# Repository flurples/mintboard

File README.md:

# mintboard
a 40% bluetooth keyboard built into an altoids tin

build video: https://youtu.be/VZ1lAV-ThZo

## you will need
- an altoids tin
- a mintboard pcb (with diodes and switches)
- 1x top and 1x bottom housings
- keycaps ( 32x 1u, 2x 1.25u, 4x 1.5u, 2x 1.75u, 1x 4u)
- a nice!nano
- a small battery (I used a [301230](https://typeractive.xyz/products/lithium-battery-110mah?_pos=1&_sid=1f1b588b2&_ss=r) 110 mah lithium battery from typeractive)
- a [OS202011MA0QN1](https://www.digikey.com/en/products/detail/c-k/OS202011MA0QN1/1981434?so=84718120&content=productdetail_US&mkt_tok=MDI4LVNYSy01MDcAAAGQVwdjiVGonvzkfjpSeKMOLfsL14AKEAxTyVseBkvXUuhdkCoQ9XYS7CoJXYxmb_hU999OJmHqsBVxQt5MaQLbL1UVmK6itZdC7dEBY8wV) or equivalent power switch
- 4x m2 screws
- double sided tape
- a dremel or something to cut the altoids tin with

## notes
- pcb production files can be found in mintboard/pcb/production
- bom files were created for jlcpcb's parts library in 2023; double check correct components before ordering
- use the provided .uf2 file to flash the nice!nano, or build your own firmware if you want. the zmk build files were made for an older version of zmk so they will likely not work without some modification.

## disclaimer
I do not sell any products, and I am not affiliated with any vendors who claim to sell my designs. if you choose to support these vendors, I am not responsible for any issues you may encounter with them.

## gallery

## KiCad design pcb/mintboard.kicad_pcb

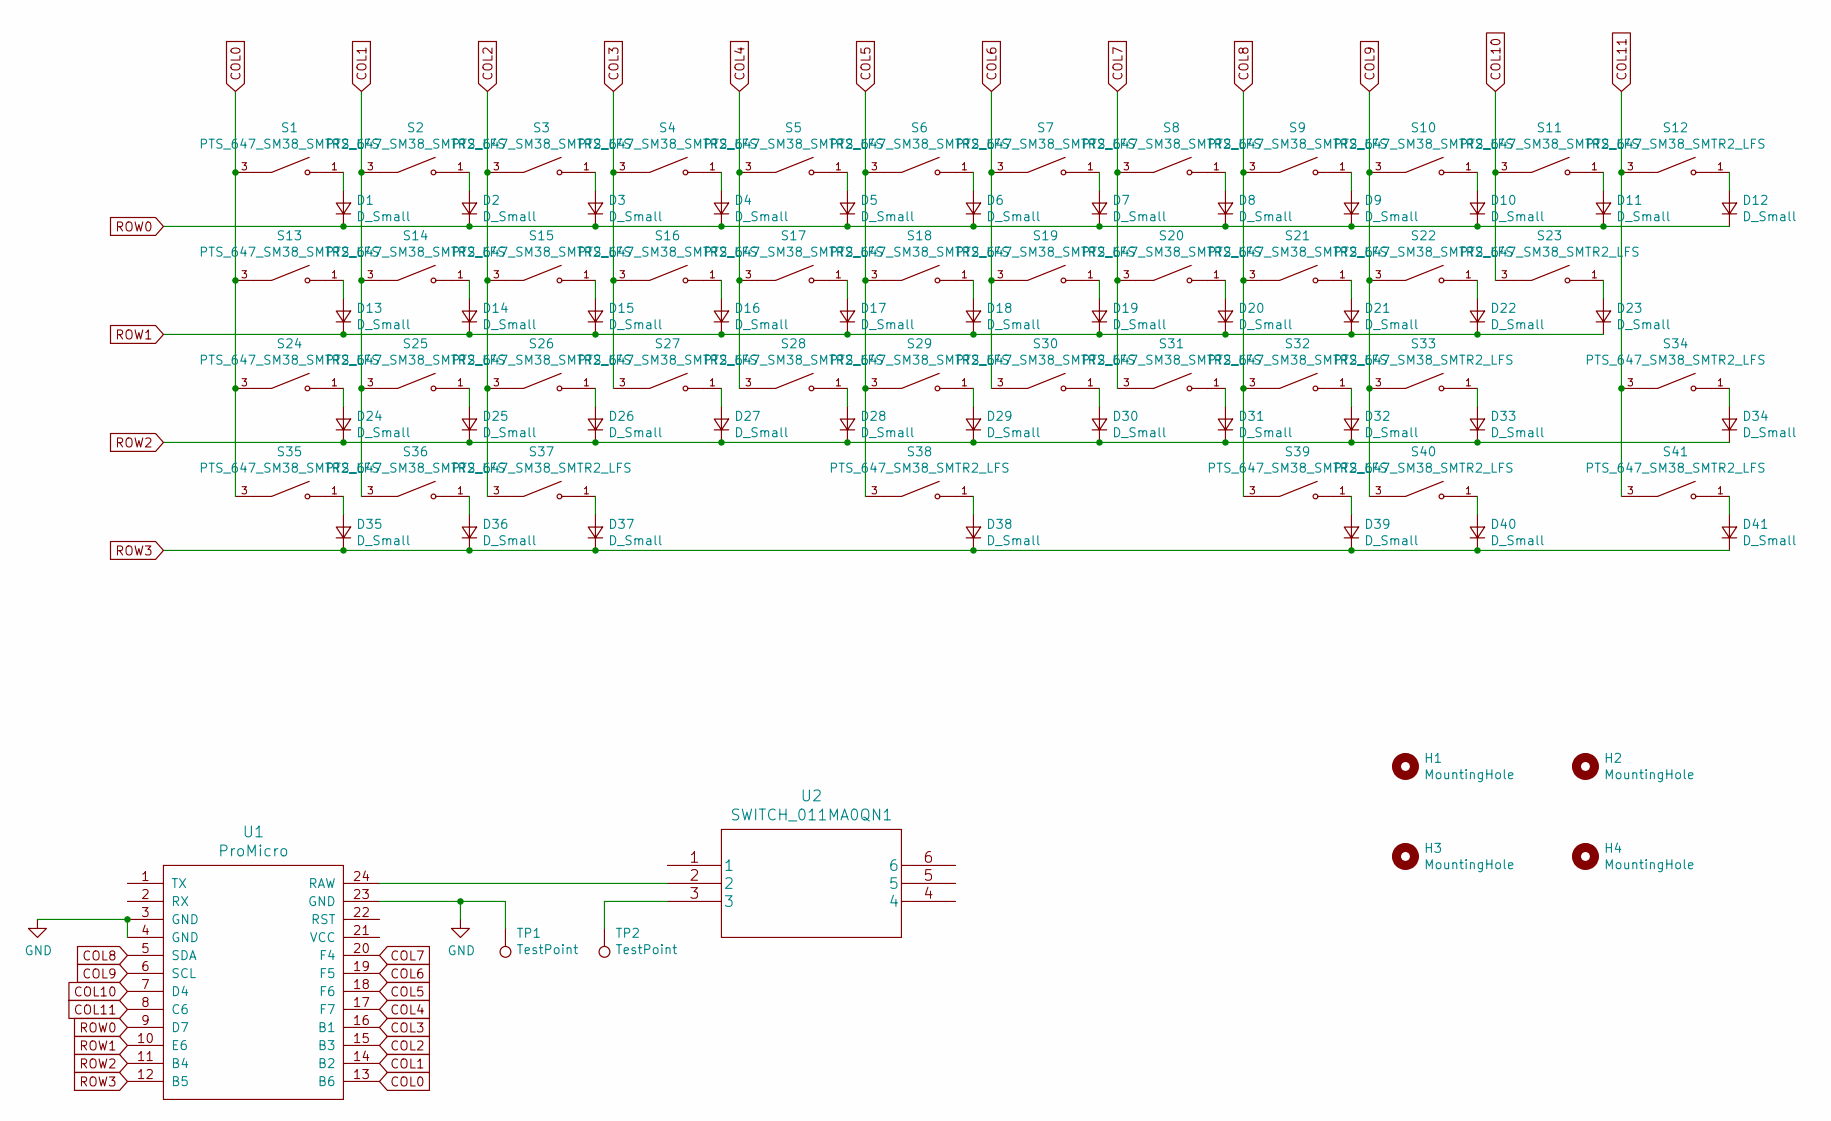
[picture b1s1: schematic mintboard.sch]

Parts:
D1, D2, D3, D4, D5, D6, D7, D8, D9, D10, D11, D12, D13, D14, D15, D16, D17, D18, D19, D20, D21, D22, D23, D24, D25, D26, D27, D28, D29, D30, D31, D32, D33, D34, D35, D36, D37, D38, D39, D40, D41: D_Small; D_SOD-123
H1, H2, H3, H4: MountingHole; MountingHole_2.5mm
S1, S2, S3, S4, S5, S6, S7, S8, S9, S10, S11, S12, S13, S14, S15, S16, S17, S18, S19, S20, S21, S22, S23, S24, S25, S26, S27, S28, S29, S30, S31, S32, S33, S34, S35, S36, S37, S38, S39, S40, S41: PTS_647_SM38_SMTR2_LFS; SW_PTS_647_SM38_SMTR2_LFS_1133; PARTREV 11 Jun 19
TP1, TP2: TestPoint; TestPoint_THTPad_D2.0mm_Drill1.0mm
U1: ProMicro; ProMicro-SMD
U2: SWITCH_011MA0QN1; OS202011MA0QN1

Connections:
COL0: S1.3, S13.3, S24.3, S35.3, U1.13 (B6)
COL1: S2.3, S14.3, S25.3, S36.3, U1.14 (B2)
COL2: S3.3, S15.3, S26.3, S37.3, U1.15 (B3)
COL3: S4.3, S16.3, S27.3, U1.16 (B1)
COL4: S5.3, S17.3, S28.3, U1.17 (F7)
COL5: S6.3, S18.3, S29.3, S38.3, U1.18 (F6)
COL6: S7.3, S19.3, S30.3, U1.19 (F5)
COL7: S8.3, S20.3, S31.3, U1.20 (F4)
COL8: S9.3, S21.3, S32.3, S39.3, U1.5 (SDA)
COL9: S10.3, S22.3, S33.3, S40.3, U1.6 (SCL)
COL10: S11.3, S23.3, U1.7 (D4)
COL11: S12.3, S34.3, S41.3, U1.8 (C6)
GND: TP1.1, U1.3 (GND), U1.4 (GND), U1.23 (GND)
unnamed: D1.2 (A), S1.1
unnamed: D2.2 (A), S2.1
unnamed: D3.2 (A), S3.1
unnamed: D4.2 (A), S4.1
unnamed: D5.2 (A), S5.1
unnamed: D6.2 (A), S6.1
unnamed: D7.2 (A), S7.1
unnamed: D8.2 (A), S8.1
unnamed: D9.2 (A), S9.1
unnamed: D10.2 (A), S10.1
unnamed: D11.2 (A), S11.1
unnamed: D12.2 (A), S12.1
unnamed: D13.2 (A), S13.1
unnamed: D14.2 (A), S14.1
unnamed: D15.2 (A), S15.1
unnamed: D16.2 (A), S16.1
unnamed: D17.2 (A), S17.1
unnamed: D18.2 (A), S18.1
unnamed: D19.2 (A), S19.1
unnamed: D20.2 (A), S20.1
unnamed: D21.2 (A), S21.1
unnamed: D22.2 (A), S22.1
unnamed: D23.2 (A), S23.1
unnamed: D24.2 (A), S24.1
unnamed: D25.2 (A), S25.1
unnamed: D26.2 (A), S26.1
unnamed: D27.2 (A), S27.1
unnamed: D28.2 (A), S28.1
unnamed: D29.2 (A), S29.1
unnamed: D30.2 (A), S30.1
unnamed: D31.2 (A), S31.1
unnamed: D32.2 (A), S32.1
unnamed: D33.2 (A), S33.1
unnamed: D34.2 (A), S34.1
unnamed: D35.2 (A), S35.1
unnamed: D36.2 (A), S36.1
unnamed: D37.2 (A), S37.1
unnamed: D38.2 (A), S38.1
unnamed: D39.2 (A), S39.1
unnamed: D40.2 (A), S40.1
unnamed: D41.2 (A), S41.1
unnamed: TP2.1, U2.3
unnamed: U1.24 (RAW), U2.2
ROW0: D1.1 (K), D2.1 (K), D3.1 (K), D4.1 (K), D5.1 (K), D6.1 (K), D7.1 (K), D8.1 (K), D9.1 (K), D10.1 (K), D11.1 (K), D12.1 (K), U1.9 (D7)
ROW1: D13.1 (K), D14.1 (K), D15.1 (K), D16.1 (K), D17.1 (K), D18.1 (K), D19.1 (K), D20.1 (K), D21.1 (K), D22.1 (K), D23.1 (K), U1.10 (E6)
ROW2: D24.1 (K), D25.1 (K), D26.1 (K), D27.1 (K), D28.1 (K), D29.1 (K), D30.1 (K), D31.1 (K), D32.1 (K), D33.1 (K), D34.1 (K), U1.11 (B4)
ROW3: D35.1 (K), D36.1 (K), D37.1 (K), D38.1 (K), D39.1 (K), D40.1 (K), D41.1 (K), U1.12 (B5)

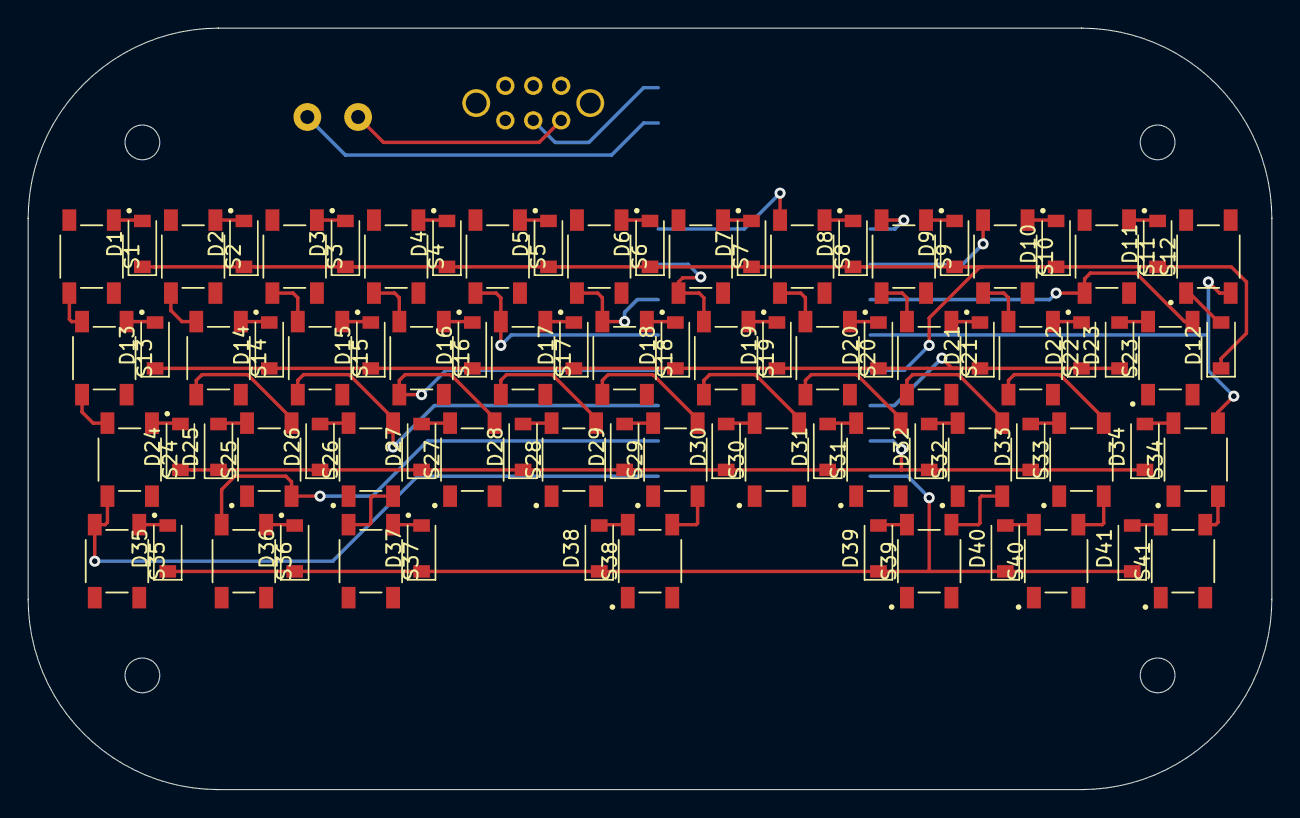
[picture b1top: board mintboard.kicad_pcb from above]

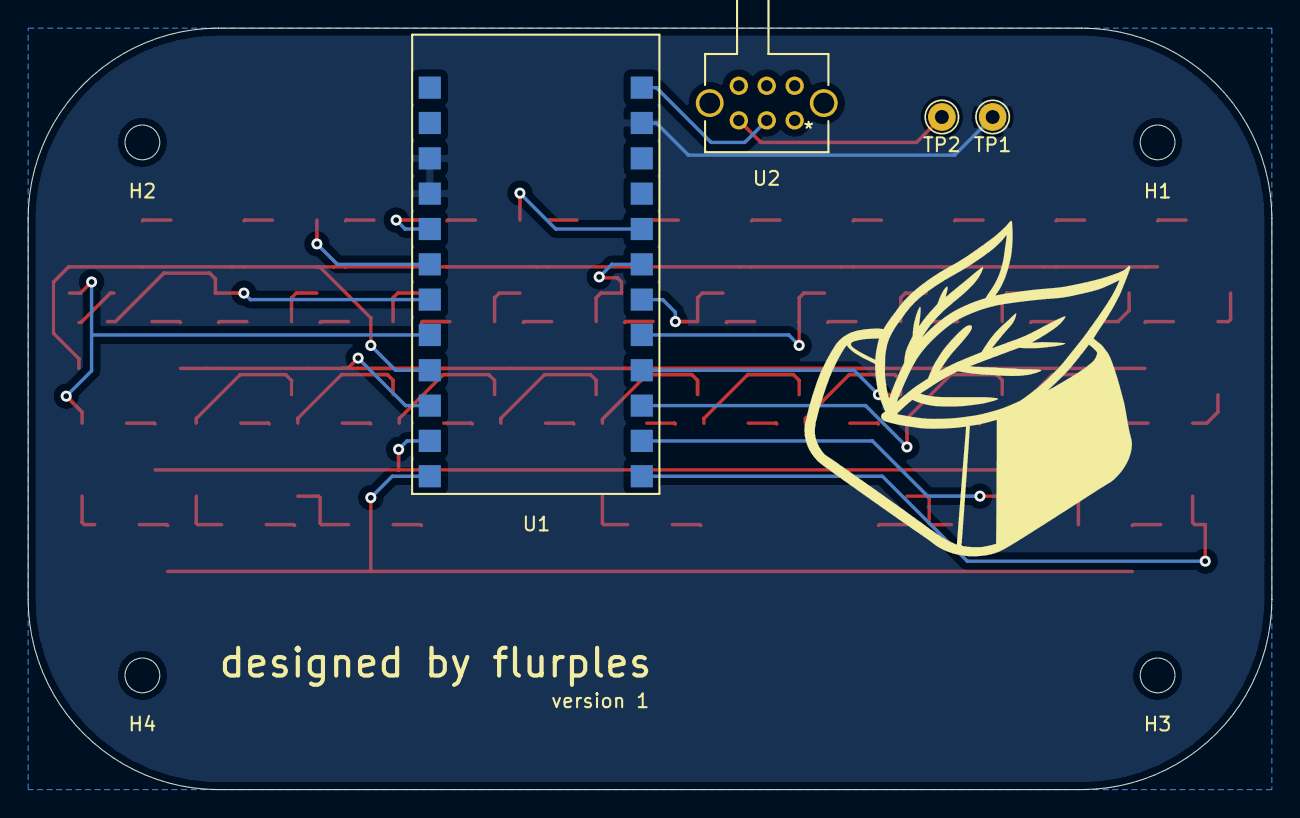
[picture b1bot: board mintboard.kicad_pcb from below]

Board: 2 copper layers, 89.4 x 54.8 mm, 90 parts (8 on the bottom side), 60 nets.

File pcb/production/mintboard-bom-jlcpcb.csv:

Comment,Designator,Footprint,LCSC Part Number
D_Small,"D1,D2,D3,D4,D5,D6,D7,D8,D9,D10,D11,D12,D13,D14,D15,D16,D17,D18,D19,D20,D21,D22,D23,D24,D25,D26,D27,D28,D29,D30,D31,D32,D33,D34,D35,D36,D37,D38,D39,D40,D41",Diode_SMD:D_SOD-123,C81598
PTS_647_SM38_SMTR2_LFS,"S1,S2,S3,S4,S5,S6,S7,S8,S9,S10,S11,S12,S13,S14,S15,S16,S17,S18,S19,S20,S21,S22,S23,S24,S25,S26,S27,S28,S29,S30,S31,S32,S33,S34,S35,S36,S37,S38,S39,S40,S41",button1:SW_PTS_647_SM38_SMTR2_LFS_1133,C2689502

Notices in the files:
parts and their libraries:
Copyright 2016 Accelerated Designs. All rights reserved.
